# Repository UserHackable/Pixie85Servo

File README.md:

## Pixie85Servo 

### Board dimensions

* (110000, 110000) original units
* (1.1000, 1.1000) inches
* (27.9400, 27.9400) mm

| Front | Back |
| --- | --- |
|  |  |

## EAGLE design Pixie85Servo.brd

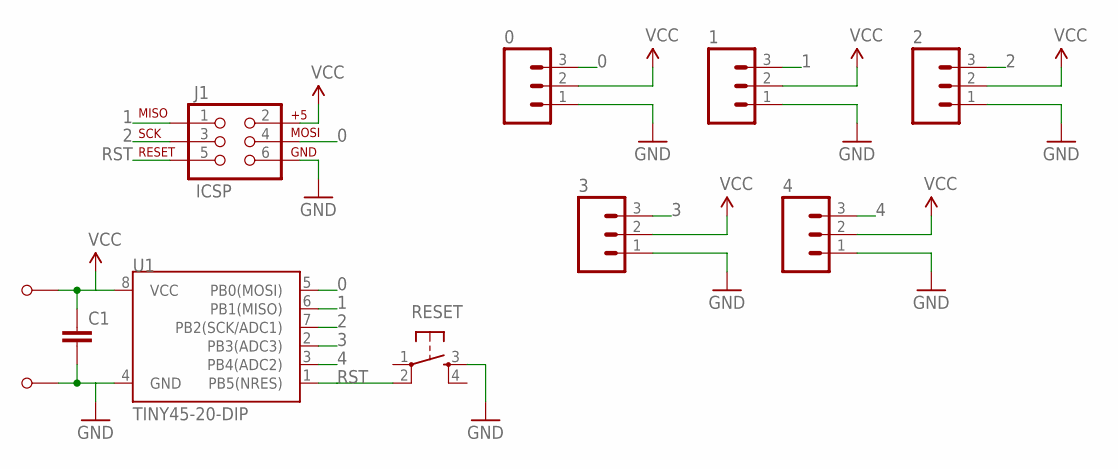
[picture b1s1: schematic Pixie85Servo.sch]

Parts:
0, 1, 2, 3, 4: M03PTH; 1X03
+: M1; M1_NO_STRAIN
-: M1; M1_NO_STRAIN
C1: CAPPTH; CAP-PTH-SMALL
J1: ICSP; 2X3-NS
RESET: TAC_SWITCHPTH; TACTILE-PTH
U1: TINY45-20-DIP; DIP08

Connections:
0: 0.3, J1.4 (MOSI), U1.5 (PB0(MOSI))
1: 1.3, J1.1 (MISO), U1.6 (PB1(MISO))
2: 2.3, J1.3 (SCK), U1.7 (PB2(SCK/ADC1))
3: 3.3, U1.2 (PB3(ADC3))
4: 4.3, U1.3 (PB4(ADC2))
GND: 0.1, 1.1, 2.1, 3.1, 4.1, -.P$1, C1.2, J1.6 (GND), RESET.3, U1.4 (GND)
RST: J1.5 (RST), RESET.2, U1.1 (PB5(NRES))
VCC: 0.2, 1.2, 2.2, 3.2, 4.2, +.P$1, C1.1, J1.2 (V+), U1.8 (VCC)

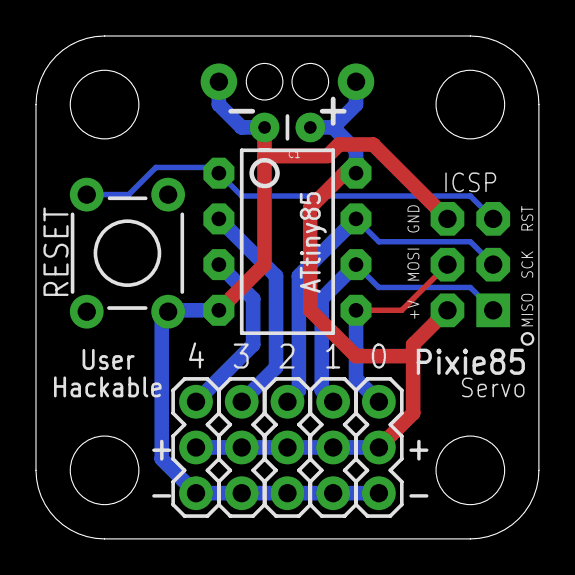
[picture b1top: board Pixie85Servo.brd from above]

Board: 2 copper layers, 27.9 x 27.9 mm, 11 parts (0 on the bottom side), 8 nets.

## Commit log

2016-03-26 updating
2016-04-06 updating makefile
2016-04-07 from Makefile

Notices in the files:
parts and their libraries:
SparkFun-DigitalIC: Licensing: Creative Commons ShareAlike 4.0 International - https://creativecommons.org/licenses/by-sa/4.0
